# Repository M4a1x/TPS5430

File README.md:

# TPS5430

This is a small DC-DC Buck converter board based on the TPS5430 from TI specifically intended to be ordered from [JLCPCB](jlcpcb.com/) with few "extended parts". This was a practice project for me, so please feel free to point out any [issues](https://github.com/M4a1x/TPS5430/issues).

## Features

* V<sub>in</sub> = 5.5V..36V
* V<sub>in<sub>min</sub></sub> = 1.15 * V<sub>out</sub> (see Datasheet Section 8.2.1.2.8.1)
* V<sub>in<sub>max</sub></sub> = 8.33 * (V<sub>out</sub> + 0.5) (see Datasheet Section 8.2.1.2.8.1)
* V<sub>out</sub> = 1.8V/3.3V/5V/12V (choose via solder bridge)
* Reverse polarity protection with AO3401A p-MOSFET
* 3A (hold)/6A (trip) polyfuse input protection
* The board can be powered with a 2.1mm/5.5mm "standard" Arduino compatible barrel jack connector.
* Status LED

## Schematic

The design was done in [KiCAD 6 nightly (aka 5.99)](https://www.kicad.org/) and follows the [TPS5430 datasheet (Section 8.2.1)](https://www.ti.com/lit/ds/symlink/tps5430.pdf) reasonably close in the schmatic as well as the layout (Section 10.2).

Deviations are:

* 2x 100uF tantalum capacitors instead of 1x 220uF, since those are basic parts at JLCPCB
* As suggested a 10uF output bypass capacitor is added
* 4x 10uF input capacitors instead of only 1x
* Multiple output voltage options through increased Inductor (47uH instead of 15uH) and solder jumpers. All outputs should work with the full 3A

## License

Licensed under CERN-OHL-S v2 or any later version. See `LICENSE` for more information.

## Contact

Max Stabel - [https://max.stabel.family/](https://max.stabel.family)

Project Link: [https://github.com/M4a1x/TPS5430](https://github.com/M4a1x/TPS5430)

## Acknowledgements

* [Philip Salamony](https://philsal.co.uk/) and his [BananaSchplit Project](https://github.com/pms67/BananaSchplit) and [Video](https://www.youtube.com/watch?v=qXWYXxDokv4)
* [ugurozkan52/TPS5430_Power_Module](https://github.com/ugurozkan52/TPS5430_Power_Module) which inspired me to add the output voltage jumpers

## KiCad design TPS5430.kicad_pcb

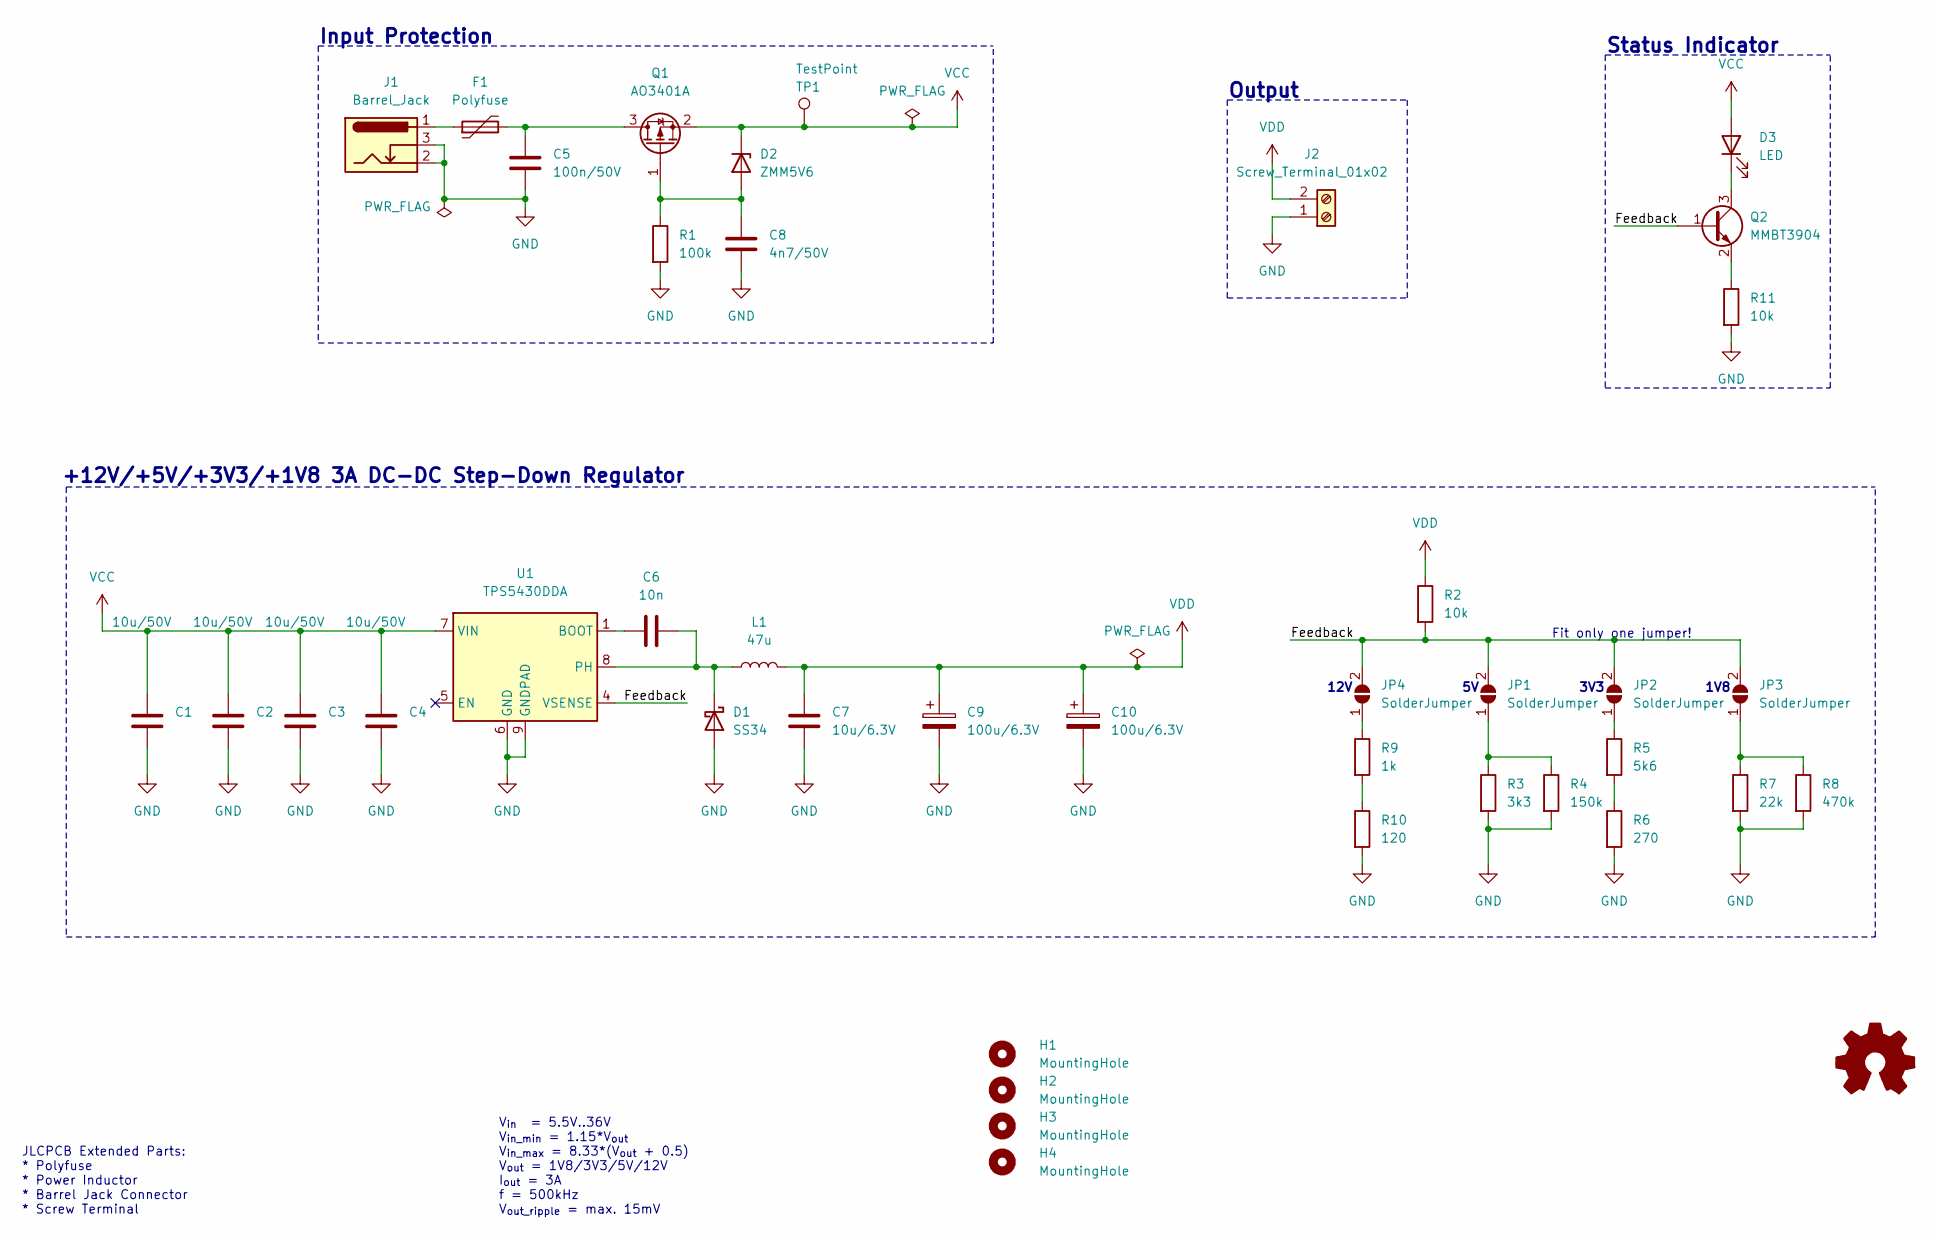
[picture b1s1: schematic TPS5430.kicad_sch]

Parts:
C1, C2, C3, C4: 10u/50V; C_1206_3216Metric; MPN CL31A106KBHNNNE; LCSC C13585
C5: 100n/50V; C_0603_1608Metric; MPN CC0603KRX7R9BB104; LCSC C14663
C6: 10n; C_0402_1005Metric; MPN CL05B103KB5NNNC; LCSC C15195
C7: 10u/6.3V; C_0402_1005Metric; MPN CL05A106MQ5NUNC; LCSC C15525
C8: 4n7/50V; C_0402_1005Metric; MPN 0402B472K500NT; LCSC C1538
C9, C10: 100u/6.3V; CP_EIA-3528-21_Kemet-B; MPN TAJB107K006RNJ; LCSC C16133
D1: SS34; D_SMA; MPN SS34; LCSC C8678
D2: ZMM5V6; D_MiniMELF; MPN ZMM5V6; LCSC C8062
D3: LED; LED_0603_1608Metric; MPN 19-217/GHC-YR1S2/3T; LCSC C72043
F1: Polyfuse; Fuse_1206_3216Metric; MPN 1206L300SLTHYR; LCSC C207041
H1, H2, H3, H4: MountingHole; MountingHole_2.2mm_M2_ISO7380
J1: Barrel_Jack; DC-005-5A-2.0-SMT; MPN DC-005-5A-2.0-SMT; LCSC C319134
J2: Screw_Terminal_01x02; TerminalBlock_Phoenix_PT-1,5-2-3.5-H_1x02_P3.50mm_Horizontal; MPN XY302V-3.5-2P; LCSC C784940
JP1, JP2, JP3, JP4: SolderJumper; SolderJumper-2_P1.3mm_Open_RoundedPad1.0x1.5mm
L1: 47u; L_Sunlord_MWSA1004S_10x11.5x4mm; MPN MWSA1004S-470MT; LCSC C408491
LOGO1: Logo_Open_Hardware_Small; OSHW-Logo_11.4x12mm_Copper
Q1: AO3401A; SOT-23; MPN AO3401A; LCSC C15127
Q2: MMBT3904; SOT-23; MPN MMBT3904; LCSC C20526
R1: 100k; R_0402_1005Metric; MPN 0402WGF1003TCE; LCSC C25741
R2: 10k; R_0402_1005Metric; MPN 0402WGF1002TCE; LCSC C25744
R3: 3k3; R_0402_1005Metric; MPN 0402WGF3301TCE; LCSC C25890
R4: 150k; R_0402_1005Metric; MPN 0402WGF1503TCE; LCSC C25755
R5: 5k6; R_0402_1005Metric; MPN 0402WGF5601TCE; LCSC C25908
R6: 270; R_0603_1608Metric; MPN 0603WAF2700T5E; LCSC C22966
R7: 22k; R_0402_1005Metric; MPN 0402WGF2202TCE; LCSC C25768
R8: 470k; R_0402_1005Metric; MPN 0402WGF4703TCE; LCSC C25790
R9: 1k; R_0402_1005Metric; MPN 0402WGF1001TCE; LCSC C11702
R10: 120; R_0402_1005Metric; MPN 0402WGF1200TCE; LCSC C25079
R11: 10k; R_0603_1608Metric; MPN 0603WAF1002T5E; LCSC C25804
TP1: TestPoint; TestPoint_Pad_D1.0mm
U1: TPS5430DDA; TI_SO-PowerPAD-8_ThermalVias; MPN TPS5430DDAR; JLC LSOP-8_EP_3.9x4.9x1.27P

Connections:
/Feedback: JP1.2 (B), JP2.2 (B), JP3.2 (B), JP4.2 (B), Q2.1 (B), R2.2, U1.4 (VSENSE)
GND: C1.2, C2.2, C3.2, C4.2, C5.2, C7.2, C8.2, C9.2, C10.2, D1.2 (A), J1.2, J1.3, J2.1, R1.2, R3.2, R4.2, R6.2, R7.2, R8.2, R10.2, R11.2, U1.6 (GND), U1.9 (GNDPAD)
unnamed: C5.1, F1.2, Q1.3 (D)
unnamed: C6.1, U1.1 (BOOT)
unnamed: C6.2, D1.1 (K), L1.1, U1.8 (PH)
unnamed: C8.1, D2.2 (A), Q1.1 (G), R1.1
unnamed: D3.1 (K), Q2.3 (C)
unnamed: F1.1, J1.1
unnamed: JP1.1 (A), R3.1, R4.1
unnamed: JP2.1 (A), R5.1
unnamed: JP3.1 (A), R7.1, R8.1
unnamed: JP4.1 (A), R9.1
unnamed: Q2.2 (E), R11.1
unnamed: R5.2, R6.1
unnamed: R9.2, R10.1
VCC: C1.1, C2.1, C3.1, C4.1, D2.1 (K), D3.2 (A), Q1.2 (S), TP1.1, U1.7 (VIN)
VDD: C7.1, C9.1, C10.1, J2.2, L1.2, R2.1

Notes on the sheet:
Fit only one jumper!
1V8
Status Indicator
JLCPCB Extended Parts: * Polyfuse * Power Inductor * Barrel Jack Connector * Screw Terminal
3V3
Output
12V
Input Protection
+12V/+5V/+3V3/+1V8 3A DC-DC Step-Down Regulator
V_{in} = 5.5V..36V V_{in_min} = 1.15*V_{out} V_{in_max} = 8.33*(V_{out} + 0.5) V_{out} = 1V8/3V3/5V/12V I_{out} = 3A f = 500kHz V_{out_ripple} = max. 15mV

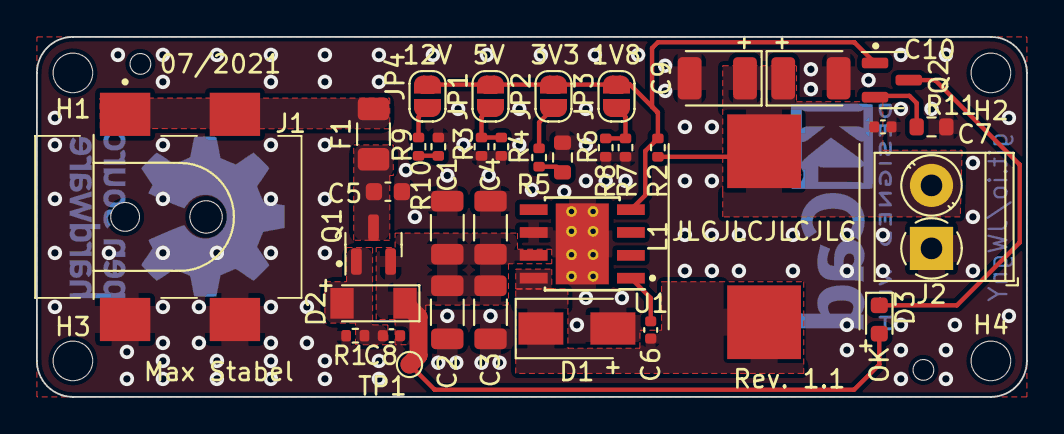
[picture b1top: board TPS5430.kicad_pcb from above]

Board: 2 copper layers, 55.0 x 20.0 mm, 41 parts (1 on the bottom side), 17 nets.

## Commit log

2021-07-15 Add page description
2021-07-15 Gerber re-export
2021-07-15 Add library with used extra parts
2021-07-15 Add renders/printouts
2021-07-15 Update .gitignore to add JLCPCB order information
2021-07-15 Add README.md and LICENSE
2021-07-16 Add License notice in files and on the PCB
2021-07-16 Fix Readme link
2021-07-17 Add TP & 12V SolderJumper
2021-07-17 Add status led & reverse polarity simulations
2021-07-17 Fix led_drive simulation
2021-07-17 Add Status LED
2021-07-17 Add status LED & fix reverse polarity protection
2022-03-12 Dim status LED and update to KiCAD 6
2022-03-13 Add LTSpice to .gitignore
2022-03-13 LTSpice: Change LED resistor to 10k as well
2022-03-13 Bump version to 1.1.1 for dimmed LED
